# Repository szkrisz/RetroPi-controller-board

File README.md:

# RetroPi-controller-board
This board helps connecting two joystick with 18 buttons to a RaspberryPi (B+) configurable with MK-ARCADE_JOY_RPI

With this PCB board you can connect a Rasberry Pi B+ 40pin header to two identical joystic and 18 button.
In Retropie program you can use the mk_arcade_joystick_rpi kernel module to configure.
https://github.com/recalbox/mk_arcade_joystick_rpi

You can use a normal 40 pin IDE cable to connect the board to the Raspberry Pi. 

ATTENTION!! Use the old 40pin cable not the new 80 pin cable, becuse the new has grounding on every line witch makes shortcut.
Correct cable: https://electronics.stackexchange.com/questions/34867/wire-gauge-of-40-pin-ide-cable
Compare: http://www.pcstats.com/articleimages/200504/hddinstall_idecable.jpg

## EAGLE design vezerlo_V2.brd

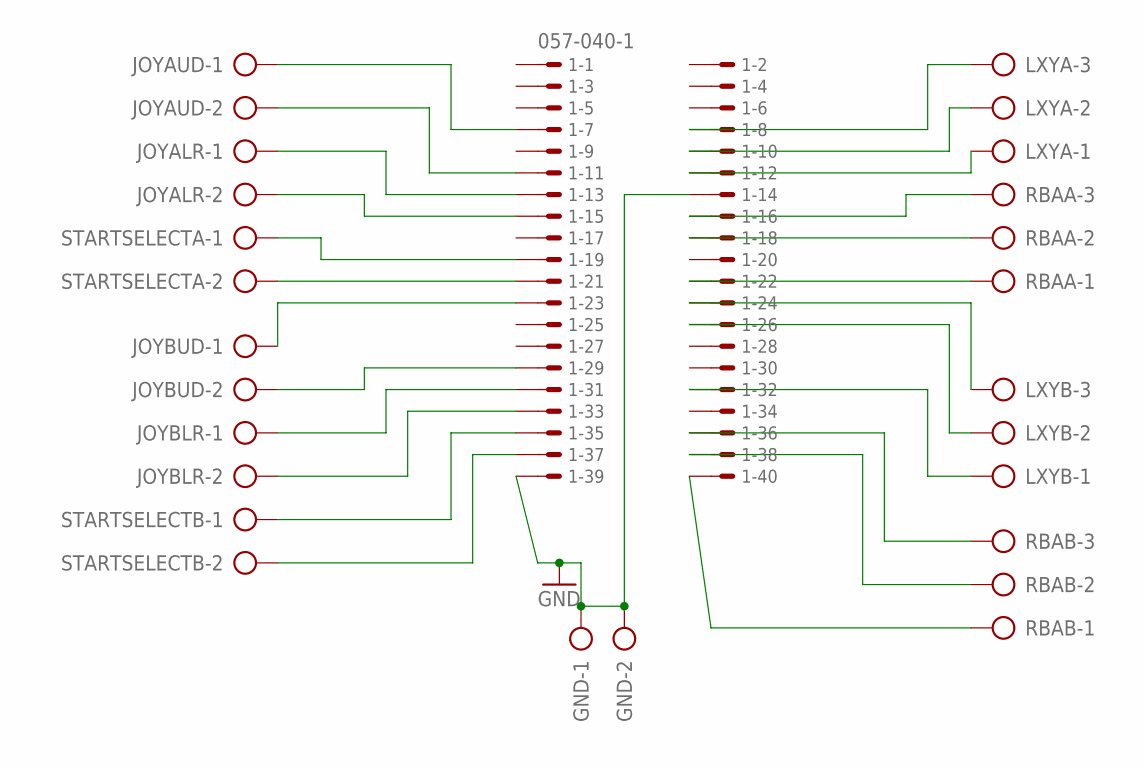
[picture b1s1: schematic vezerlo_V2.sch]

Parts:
1: 057-040-1
GND: AK500/2-H
JOYALR: AK500/2-H
JOYAUD: AK500/2-H
JOYBLR: AK500/2-H
JOYBUD: AK500/2-H
LXYA: AK500/3-H
LXYB: AK500/3-H
RBAA: AK500/3-H
RBAB: AK500/3-H
STARTSELECTA: AK500/2-H
STARTSELECTB: AK500/2-H

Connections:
GND: 1.14, 1.39, GND.1, GND.2
unnamed: 1.7, JOYAUD.1
unnamed: 1.11, JOYAUD.2
unnamed: 1.13, JOYALR.1
unnamed: 1.15, JOYALR.2
unnamed: 1.19, STARTSELECTA.1
unnamed: 1.21, STARTSELECTA.2
unnamed: 1.23, JOYBUD.1
unnamed: 1.29, JOYBUD.2
unnamed: 1.31, JOYBLR.1
unnamed: 1.33, JOYBLR.2
unnamed: 1.35, STARTSELECTB.1
unnamed: 1.37, STARTSELECTB.2
unnamed: 1.8, LXYA.3
unnamed: 1.10, LXYA.2
unnamed: 1.12, LXYA.1
unnamed: 1.16, RBAA.3
unnamed: 1.18, RBAA.2
unnamed: 1.22, RBAA.1
unnamed: 1.24, LXYB.3
unnamed: 1.26, LXYB.2
unnamed: 1.32, LXYB.1
unnamed: 1.36, RBAB.3
unnamed: 1.38, RBAB.2
unnamed: 1.40, RBAB.1

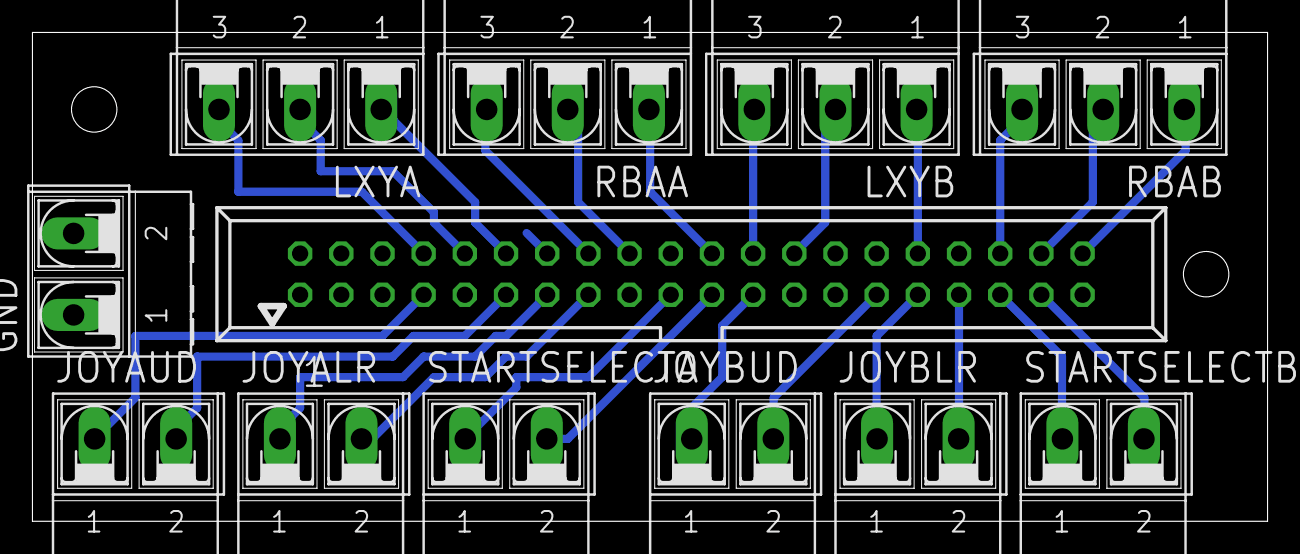
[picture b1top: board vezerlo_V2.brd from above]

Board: 2 copper layers, 76.2 x 30.2 mm, 12 parts (0 on the bottom side), 25 nets.
